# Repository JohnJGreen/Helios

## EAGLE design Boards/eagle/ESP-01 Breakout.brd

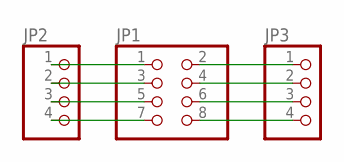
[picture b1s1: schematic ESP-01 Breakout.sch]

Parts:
JP1: PINHD-2X4; 2X04
JP2, JP3: PINHD-1X4; 1X04

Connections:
unnamed: JP1.1, JP2.1
unnamed: JP1.3, JP2.2
unnamed: JP1.5, JP2.3
unnamed: JP1.7, JP2.4
unnamed: JP1.2, JP3.1
unnamed: JP1.4, JP3.2
unnamed: JP1.6, JP3.3
unnamed: JP1.8, JP3.4

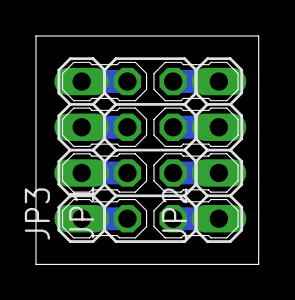
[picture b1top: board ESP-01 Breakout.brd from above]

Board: 2 copper layers, 12.4 x 12.7 mm, 3 parts (0 on the bottom side), 8 nets.

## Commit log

2017-08-30 :boom::camel: Added .gitattributes & .gitignore files
2017-08-30 Transfer from old account
